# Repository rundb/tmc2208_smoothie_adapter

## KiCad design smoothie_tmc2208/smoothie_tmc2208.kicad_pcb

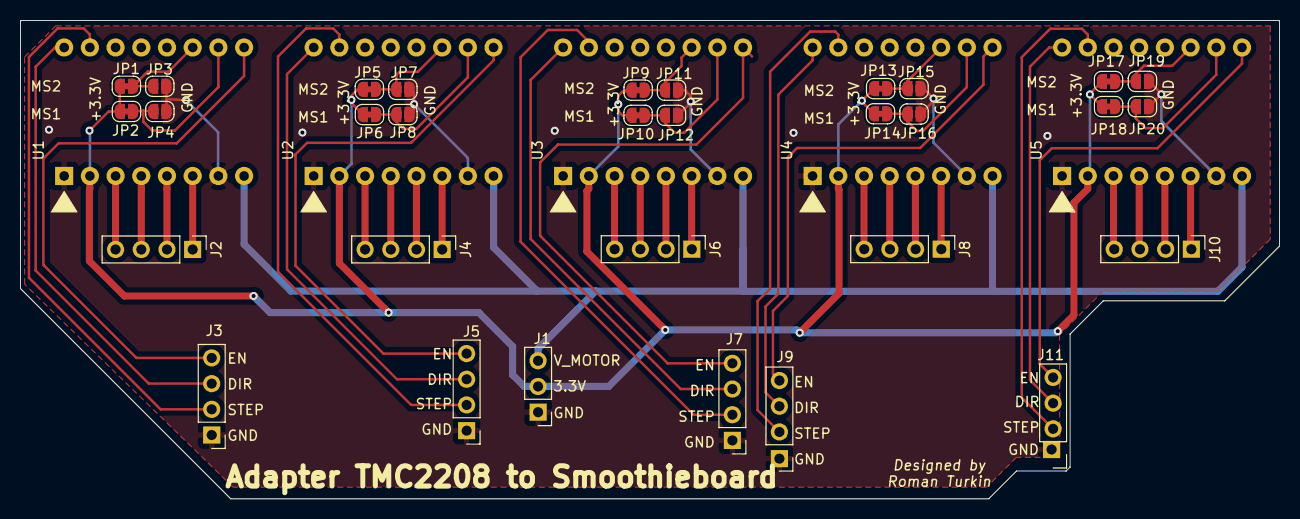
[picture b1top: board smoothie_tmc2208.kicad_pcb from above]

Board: 2 copper layers, 124.4 x 47.3 mm, 36 parts (0 on the bottom side), 48 nets.

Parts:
J1: SMOOTHIE_JP17; PinHeader_1x03_P2.54mm_Vertical
J2, J4: M2; PinHeader_1x04_P2.54mm_Vertical
J3: SMOOTHIE_JP7; PinHeader_1x04_P2.54mm_Vertical
J5: SMOOTHIE_JP9; PinHeader_1x04_P2.54mm_Vertical
J6: M3; PinHeader_1x04_P2.54mm_Vertical
J7: SMOOTHIE_JP12; PinHeader_1x04_P2.54mm_Vertical
J8: M4; PinHeader_1x04_P2.54mm_Vertical
J9: SMOOTHIE_JP15; PinHeader_1x04_P2.54mm_Vertical
J10: M5; PinHeader_1x04_P2.54mm_Vertical
J11: SMOOTHIE_JP18; PinHeader_1x04_P2.54mm_Vertical
JP1, JP2, JP5, JP6, JP9, JP10, JP13, JP14, JP17, JP18: SolderJumper_2_Bridged; SolderJumper-2_P1.3mm_Bridged_RoundedPad1.0x1.5mm
JP3, JP4, JP7, JP8, JP11, JP12, JP15, JP16, JP19, JP20: SolderJumper_2_Open; SolderJumper-2_P1.3mm_Open_RoundedPad1.0x1.5mm
U1, U2, U3, U4, U5: TMC2208-MKS_V2.0; TMC2208_MODULE

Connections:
+3V3: J1.2, JP1.1, JP2.1, JP5.1, JP6.1, JP9.1, JP10.1, JP13.1, JP14.1, JP17.1, JP18.1, U1.2, U2.2, U3.2, U4.2, U5.2
/DIR1: J3.3, U1.16
/DIR2: J5.3, U2.16
/DIR3: J7.3, U3.16
/DIR4: J9.3, U4.16
/DIR5: J11.3, U5.16
/EN1: J3.4, U1.9
/EN2: J5.4, U2.9
/EN3: J7.4, U3.9
/EN4: J9.4, U4.9
/EN5: J11.4, U5.9
/MS1_1: JP2.2, JP4.1, U1.10
/MS1_2: JP6.2, JP8.1, U2.10
/MS1_3: JP10.2, JP12.1, U3.10
/MS1_4: JP14.2, JP16.1, U4.10
/MS1_5: JP18.2, JP20.1, U5.10
/MS2_1: JP1.2, JP3.1, U1.11
/MS2_2: JP5.2, JP7.1, U2.11
/MS2_3: JP9.2, JP11.1, U3.11
/MS2_4: JP13.2, JP15.1, U4.11
/MS2_5: JP17.2, JP19.1, U5.11
/ST1: J3.2, U1.15
/ST2: J5.2, U2.15
/ST3: J7.2, U3.15
/ST4: J9.2, U4.15
/ST5: J11.2, U5.15
GND: J1.1, J3.1, J5.1, J7.1, J9.1, J11.1, JP3.2, JP4.2, JP7.2, JP8.2, JP11.2, JP12.2, JP15.2, JP16.2, JP19.2, JP20.2, U1.1, U1.7, U2.1, U2.7, U3.1, U3.7, U4.1, U4.7, U5.1, U5.7
unnamed: J2.1, U1.6
unnamed: J2.2, U1.5
unnamed: J2.3, U1.4
unnamed: J2.4, U1.3
unnamed: J4.1, U2.6
unnamed: J4.2, U2.5
unnamed: J4.3, U2.4
unnamed: J4.4, U2.3
unnamed: J6.1, U3.6
unnamed: J6.2, U3.5
unnamed: J6.3, U3.4
unnamed: J6.4, U3.3
unnamed: J8.1, U4.6
unnamed: J8.2, U4.5
unnamed: J8.3, U4.4
unnamed: J8.4, U4.3
unnamed: J10.1, U5.6
unnamed: J10.2, U5.5
unnamed: J10.3, U5.4
unnamed: J10.4, U5.3
VDD: J1.3, U1.8, U2.8, U3.8, U4.8, U5.8

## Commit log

2021-03-13 initial sources of the PCB
